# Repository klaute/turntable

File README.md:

***test***

| | |
|:---|---:|
|Content Cell|Content Cell|
|Content Cell|Content Cell|

https://www.pololu.com/product/1182/faqs

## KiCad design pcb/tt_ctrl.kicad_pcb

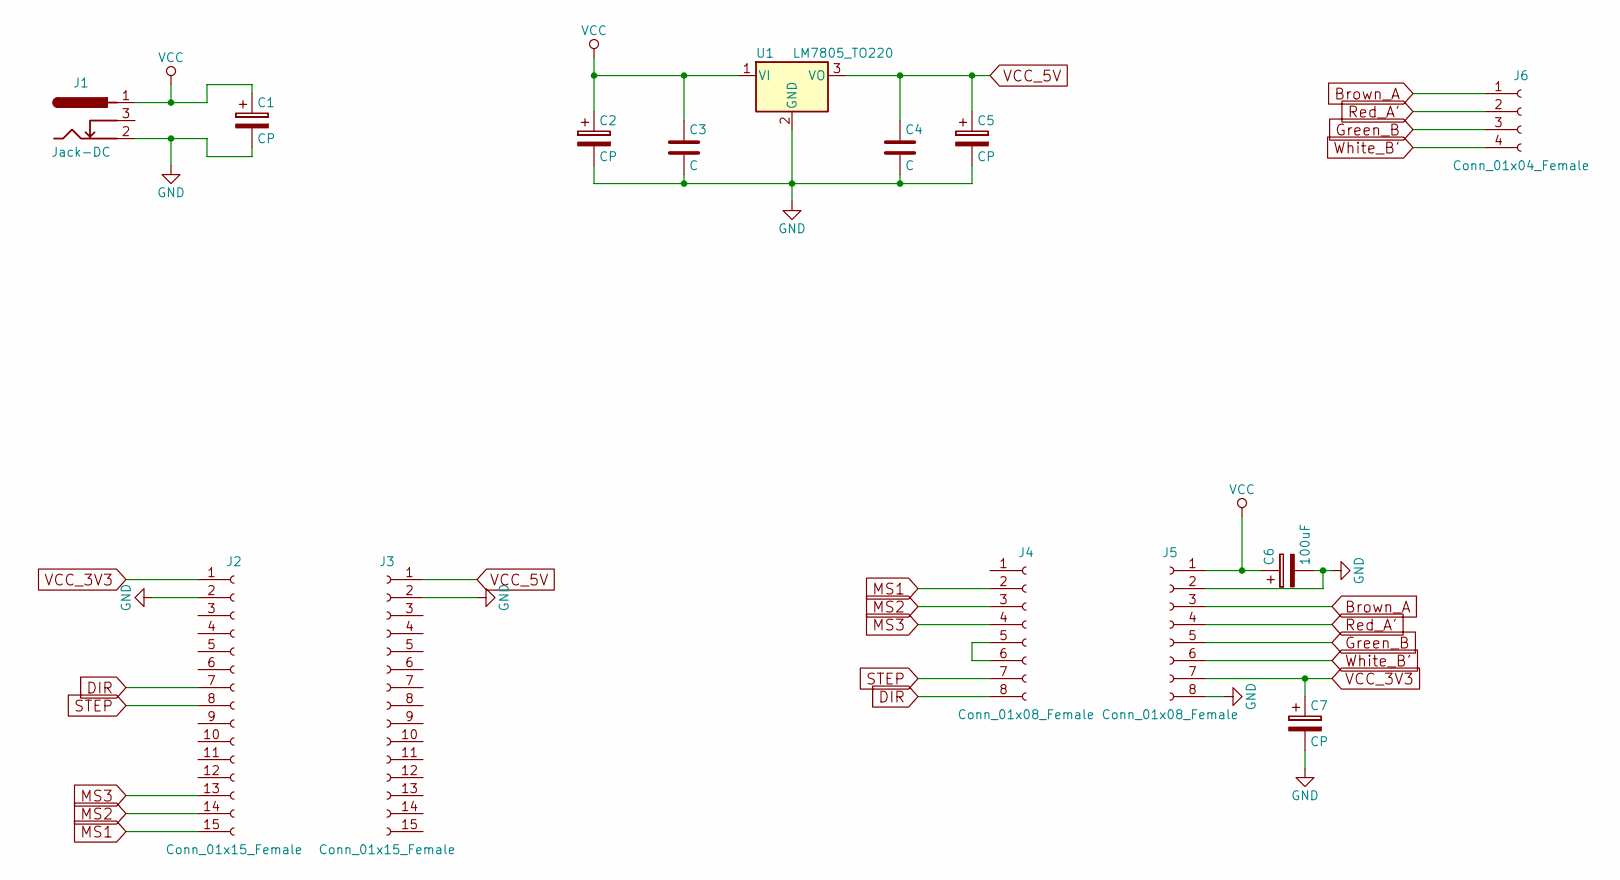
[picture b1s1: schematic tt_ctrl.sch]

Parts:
C1, C2, C5, C7: CP; CP_Radial_D5.0mm_P2.50mm
C3, C4: C; C_Disc_D5.0mm_W2.5mm_P2.50mm
C6: 100uF; CP_Radial_D5.0mm_P2.50mm
J1: Jack-DC; BARREL_JACK
J2, J3: Conn_01x15_Female; Socket_Strip_Straight_1x15_Pitch2.54mm
J4, J5: Conn_01x08_Female; Socket_Strip_Straight_1x08_Pitch2.54mm
J6: Conn_01x04_Female; Socket_Strip_Straight_1x04_Pitch2.54mm
U1: LM7805_TO220; TO-220

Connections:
Brown_A: J5.3, J6.1
DIR: J2.7, J4.8
GND: C1.2, C2.2, C3.2, C4.2, C5.2, C6.2, C7.2, J1.2, J2.2, J3.2, J5.2, J5.8, U1.2 (GND)
Green_B: J5.5, J6.3
MS1: J2.15, J4.2
MS2: J2.14, J4.3
MS3: J2.13, J4.4
unnamed: J4.5, J4.6
Red_A': J5.4, J6.2
STEP: J2.8, J4.7
VCC: C1.1, C2.1, C3.1, C6.1, J1.1, J5.1, U1.1 (VI)
VCC_3V3: C7.1, J2.1, J5.7
VCC_5V: C4.1, C5.1, J3.1, U1.3 (VO)
White_B': J5.6, J6.4

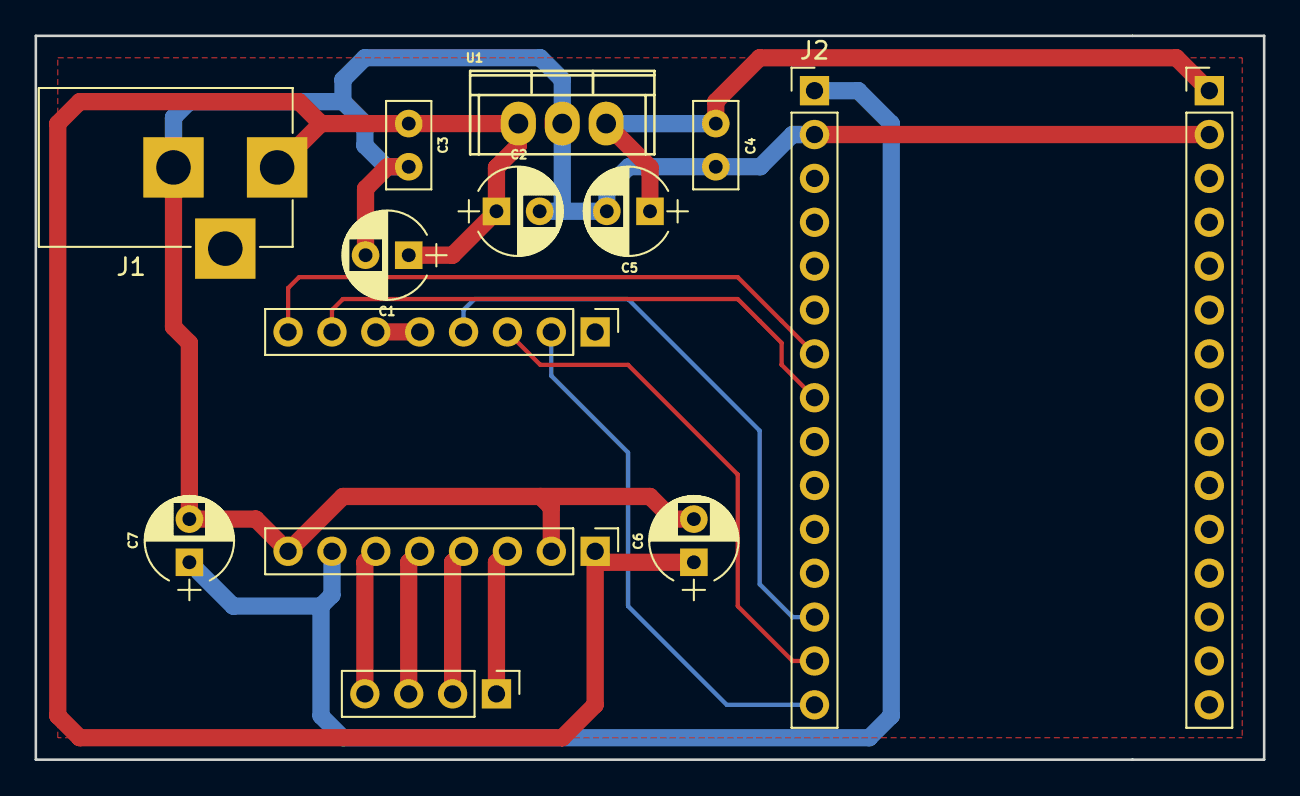
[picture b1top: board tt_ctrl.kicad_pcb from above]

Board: 2 copper layers, 71.1 x 41.9 mm, 14 parts (0 on the bottom side), 14 nets.

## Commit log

2018-04-07 Added the initial version of the turntable firmware.
2018-04-07 Webserver added.
2018-04-07 First version which can connect to an accesspoint. The webserver is also available.
2018-04-18 Wifi is working. Webserver is working. Webserver setter functionality for the variables work fine. Webbased status get functionality works. Internal HTML/JavaScript implementation of the control pana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
2018-04-18 Modified the motor setting, he is quiet faster and much louder than before.
2018-04-19 Modified the stepper motor timing.
2018-04-20 tt_eeprom_config.ino
    Added the eeprom configuration module.
2018-04-20 Moved some code to the configuration file. EEPROM save/load etc. functionality added.
2018-04-20 Debug mode disabled.
2018-04-22 Added the /WU feature to enable the web upter functionality.
2018-04-22 WebUpdater overwrites the previous set wifi settings.
2018-04-22 Disabled the webupdater wifi config code.
2018-04-22 The WebUpdater is now available but the upload fails.
2018-04-27 Set the D0 to high during the WebUpdater is enabled.
2018-04-27 Documentation added.
2018-05-18 PCB files added and doc folder update.
2018-05-18 First version of the PCB added.
2018-09-07 Update README.md
    Table test
2018-09-07 Update README.md
    Table test 2
2018-09-07 Update README.md
    Table test3
2018-09-07 Update README.md
    Test 4
2018-09-07 Update README.md
    Test 5
2018-09-07 Update README.md
    Test6
2018-09-07 Update README.md
    Test7
2018-09-07 Update README.md
    Test finished
